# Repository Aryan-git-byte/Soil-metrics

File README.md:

<div align="center">

<h1>SoilMetrics</h1>

<h4><i>A Portable AI & IoT-Based Soil Health Monitoring Device</i></h4>

</div>

---

# Overview:

SoilMetrics is an **affordable soil health monitoring system** to measure key soil parameters in real time such as **NPK, EC, pH, Moisture, and Temperature.** which will allow small farmers to make scientific decision regarding their soil health and conditions which can help them do sustainable farming.

# What can it do?
This device can measure soil moisture, temperature, pH, electrical conductivity, and NPK. and then can send all that data to a cloud server using LTE. it also offers on device touch display to view sensor readings, ai reccomendations, weather reports etc. with help of offline sd card based data logging, and rechargeable 2S 18650 its a near perfect solution to deploy on farmsites for primary soil health monitoring.

## Hardware Specifications:

- **MCU** - [ESP32-S3-WROOM1U-N16R8](https://documentation.espressif.com/esp32-s3-wroom-1_wroom-1u_datasheet_en.pdf)
- **Cellular & GPS** - [SIM7080G](https://www.simcom.com/product/SIM7080G.html)
- **Soil Sensor** - [ZTS-3002-TR-\*-N01](https://robu-prod-media.s3.ap-south-1.amazonaws.com/uploads/2025/04/R224073R224074-ZTS-3002-TR-N01.pdf)
- **Display** - [SmartElex 3.5" TFT Resistive Touch Display 320x480](https://robu.in/product/smartelex-3-5-tft-resistive-touch-display-320x480/)

## Repo Structure:

```
SoilMetrics/
│
├── assets/   images
├── cad/       CAD source files & exports
├── firmware/       ESP-IDF firmware
├── kicad/          kicad source file
├── production/     BOM & gerber
│
├── README.md
├── LICENSE
└── JOURNAL.md
```

---

# Hardware:

## Schematic:

> Contains all the power realted things of the device including Type-c for programming, barrel jack for charging, BMS circuitory, Buck Converter and LDOs

> Contains the MCU, Buttons, LTE module, Receiver, SD card, sim slot etc

## PCB:

The hardware is designed on a 4 layer PCB, The complete design files are available [here](kicad/)

---

# Enclosure
| File | Download Link | Description|
|------|---------------|------------|
|Top Body Enclosure|[here](cad/src/Top-Body.f3d)|This is the source file of the top body
|Bottom plate|[here](cad/src/Bottom-Plate.f3d)|This is the source file of the Bottom plate
|Top Body Enclosure|[here](cad/exports/Top-Body.3mf)|This is the printable file of the top body
|Top Body Enclosure|[here](cad/exports/Bottom-Plate.3mf)|This is the printable file of the top body

---

# Firmware
> **Note:** The complete firmware is not available as of now, there are lot of things that can only be written after making actual hardware, so i will update the repo with complete firmware after build. For now its just a test code.

Configure ESP-IDF

```
idf.py set-target esp32s3
```

Build

```
idf.py build
```

---

## Flashing Firmware

Connect the board using USB.

Flash

```
idf.py flash
```

Open Serial Monitor

```
idf.py monitor
```

If flashing fails, place the board into download mode according to your ESP32-S3 hardware design and retry the command.

---
# How to Assemble

1. order all the components and pcb
2. solder them
3. flash the firmware
4. test it
5. 3d print the enclousure
6. put them all together

## Enclosure:
> Enclosure is not complete yet due to the online unavailability of 3d model of the Display. After getting the display i'll update the repo with correct files

---

# Bill of Materials

The completed BOM of the components used on PCB is in [production/bom.csv](production/bom.csv).

And expect those you need to order these:
|Component | Link | Price | 
|----------|------|-------|
|SmartElex 3.5" TFT Resistive Touch Display 320x480| [here](https://robu.in/product/smartelex-3-5-tft-resistive-touch-display-320x480/)|917 rs
| ZTS-3002-TR-*-N01|[here]( https://robu.in/product/multi-parameter-sensor/)|4396 rs
|2 x 18650 batteries | [here](https://robu.in/product/sony-vtc6-18650-li-ion-3000-mah-battery/)|699 rs each
| PCB + Stencil | | Sub-8K rs

---

*Made with 🔬🧪 ~~(science)~~ by aryan-git-byte*

```
# AI USE: AI has assisted me in firmware/

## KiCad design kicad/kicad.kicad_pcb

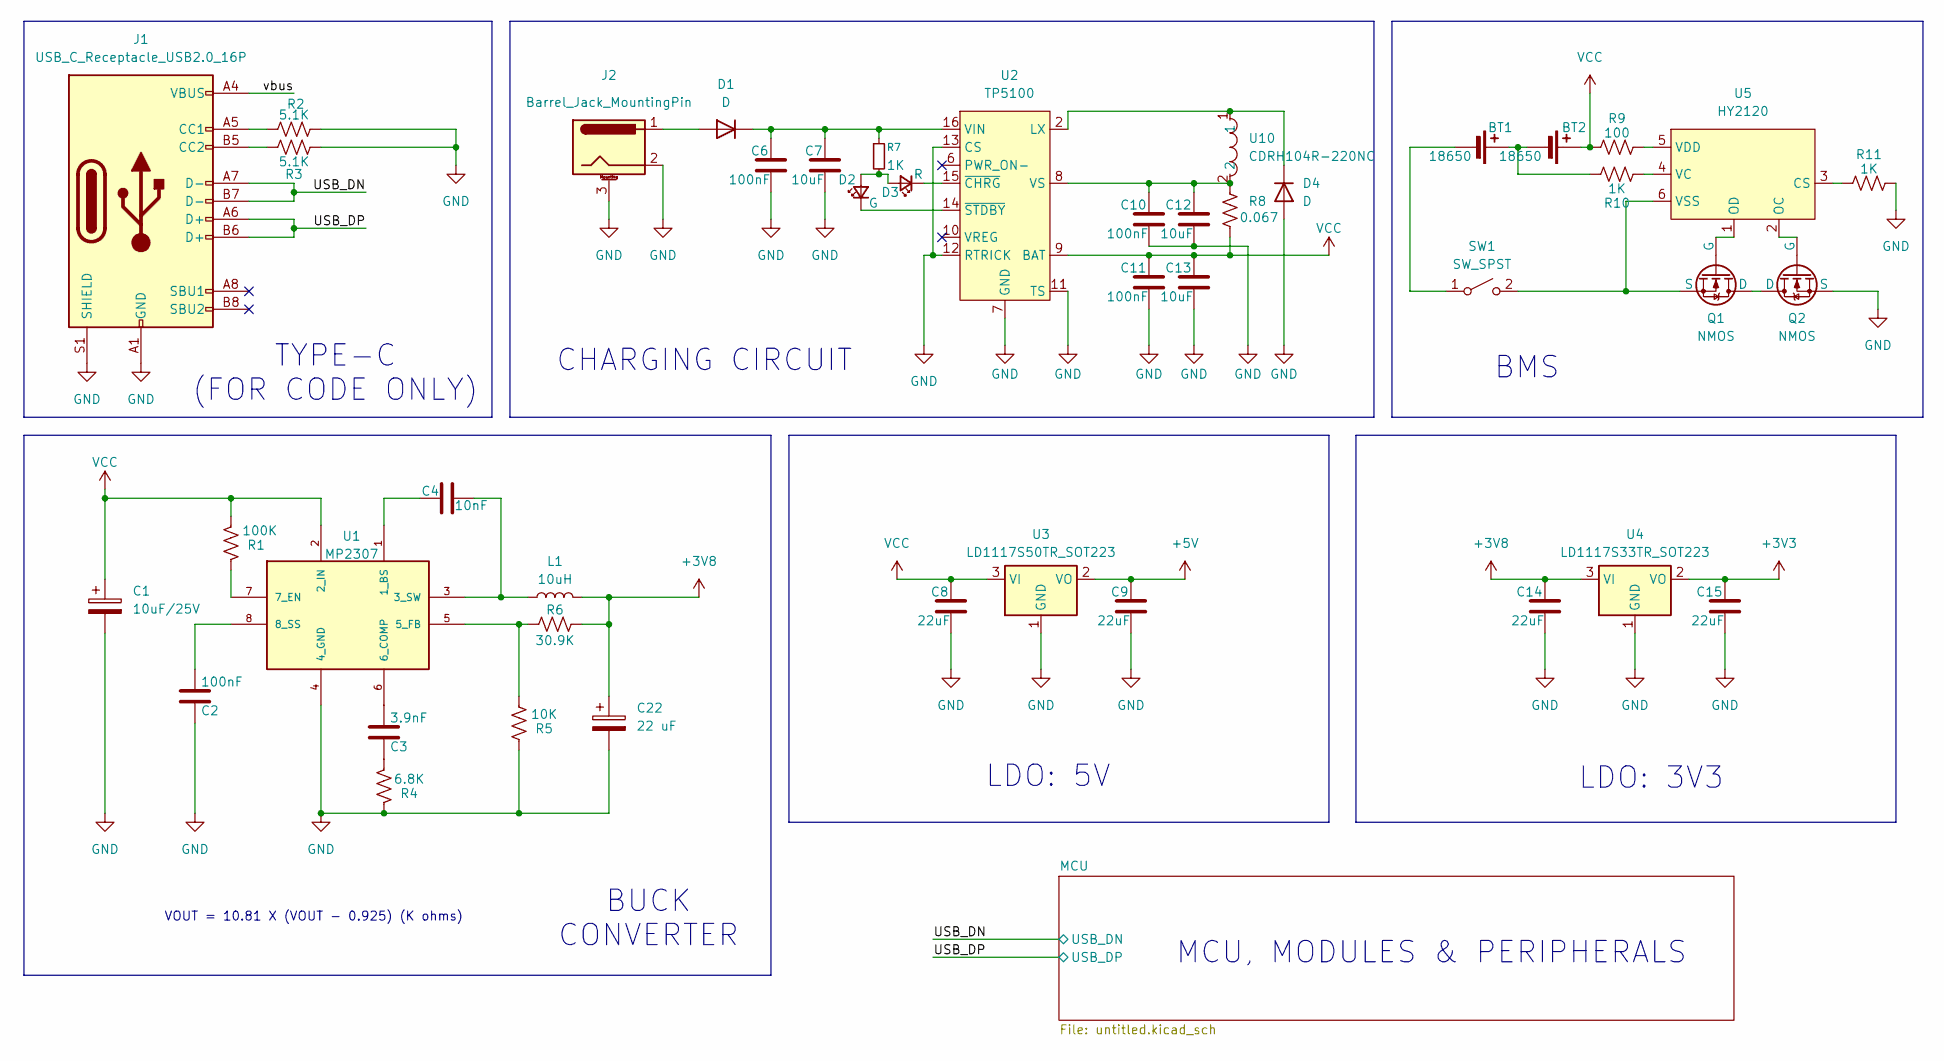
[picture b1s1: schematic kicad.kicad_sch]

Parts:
BT1, BT2: 18650; BatteryHolder_Keystone_1042_1x18650
C1: 10uF/25V; CP_Elec_6.3x5.4
C2, C6, C10, C11: 100nF; C_0805_2012Metric_Pad1.18x1.45mm_HandSolder
C3: 3.9nF; C_0805_2012Metric_Pad1.18x1.45mm_HandSolder
C4: 10nF; C_0805_2012Metric_Pad1.18x1.45mm_HandSolder
C7, C12, C13: 10uF; C_0805_2012Metric_Pad1.18x1.45mm_HandSolder
C8, C9, C14, C15: 22uF; C_0805_2012Metric_Pad1.18x1.45mm_HandSolder
C22: 22 uF; CP_Elec_5x5.3
D1, D4: D; D_SMA_Handsoldering
D2: G; LED_0805_2012Metric_Pad1.15x1.40mm_HandSolder
D3: R; LED_0805_2012Metric_Pad1.15x1.40mm_HandSolder
J1: USB_C_Receptacle_USB2.0_16P; USB_C_Receptacle_HRO_TYPE-C-31-M-12
J2: Barrel_Jack_MountingPin; BarrelJack_Horizontal
L1: 10uH; IND-SMD_L10.2-W10.0_SRR1050HA
Q1, Q2: NMOS; SOT-23
R1: 100K; R_0805_2012Metric_Pad1.20x1.40mm_HandSolder
R2, R3: 5.1K; R_0805_2012Metric_Pad1.20x1.40mm_HandSolder
R4: 6.8K; R_0805_2012Metric_Pad1.20x1.40mm_HandSolder
R5: 10K; R_0805_2012Metric_Pad1.20x1.40mm_HandSolder
R6: 30.9K; R_0805_2012Metric_Pad1.20x1.40mm_HandSolder
R7, R10, R11: 1K; R_0805_2012Metric_Pad1.20x1.40mm_HandSolder
R8: 0.067; R_1206_3216Metric_Pad1.30x1.75mm_HandSolder
R9: 100; R_0805_2012Metric_Pad1.20x1.40mm_HandSolder
SW1: SW_SPST; SW_Slide-03_Wuerth-WS-SLTV_10x2.5x6.4_P2.54mm
U1: MP2307; SOIC-8-1EP_3.9x4.9mm_P1.27mm_EP2.29x3mm_ThermalVias
U2: TP5100; QFN65P400X400X90-17N
U3: LD1117S50TR_SOT223; SOT-223-3_TabPin2
U4: LD1117S33TR_SOT223; SOT-223-3_TabPin2
U5: HY2120; SOT-23-6_Handsoldering
U10: CDRH104R-220NC; IND-SMD_L10.2-W10.0_SRR1050HA

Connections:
+3V3: C15.1, U4.2 (VO); also elsewhere on the board
+3V8: C14.1, C22.1, L1.2, R6.1, U4.3 (VI); also elsewhere on the board
+5V: C9.1, U3.2 (VO); also elsewhere on the board
/USB_DN: J1.A7 (D-), J1.B7 (D-); also elsewhere on the board
/USB_DP: J1.A6 (D+), J1.B6 (D+); also elsewhere on the board
/vbus: J1.A4 (VBUS), J1.A9 (VBUS), J1.B4 (VBUS), J1.B9 (VBUS)
GND: C1.2, C2.1, C6.2, C7.2, C8.2, C9.2, C10.2, C11.2, C12.2, C13.2, C14.2, C15.2, C22.2, D4.2 (A), J1.A1 (GND), J1.A12 (GND), J1.B1 (GND), J1.B12 (GND), J1.S1 (SHIELD), J2.2, J2.3 (MountPin_3), Q2.3 (S), R2.2, R3.1, R4.1, R5.2, R11.2, U1.4 (4_GND), U1.9 (4_GND), U2.7 (GND), U2.11 (TS), U2.12 (RTRICK), U2.13 (CS), U2.17 (EPAD), U3.1 (GND), U4.1 (GND); also elsewhere on the board
unnamed: BT1.1 (+), BT2.2 (-), R10.2
unnamed: BT1.2 (-), SW1.1 (A)
unnamed: C3.1, R4.2
unnamed: D1.2 (A), J2.1
unnamed: C6.1, C7.1, D1.1 (K), R7.1, U2.1 (VIN), U2.4 (VIN), U2.5 (VIN), U2.16 (VIN)
unnamed: D2.2 (A), D3.2 (A), R7.2
unnamed: D2.1 (K), U2.14 (~STDBY)
unnamed: D3.1 (K), U2.15 (~CHRG)
unnamed: D4.1 (K), U2.2 (LX), U2.3 (LX), U10.1
unnamed: J1.A5 (CC1), R2.1
unnamed: J1.B5 (CC2), R3.2
unnamed: Q1.1 (D), Q2.1 (D)
unnamed: Q1.2 (G), U5.1 (OD)
unnamed: Q1.3 (S), SW1.2 (B), U5.6 (VSS)
unnamed: Q2.2 (G), U5.2 (OC)
unnamed: C4.1, U1.1 (1_BS)
unnamed: C4.2, L1.1, U1.3 (3_SW)
unnamed: R5.1, R6.2, U1.5 (5_FB)
unnamed: C3.2, U1.6 (6_COMP)
unnamed: R1.1, U1.7 (7_EN)
unnamed: C2.2, U1.8 (8_SS)
unnamed: C10.1, C12.1, R8.1, U2.8 (VS), U10.2
unnamed: R11.1, U5.3 (CS)
unnamed: R10.1, U5.4 (VC)
unnamed: R9.2, U5.5 (VDD)
VCC: BT2.1 (+), C1.1, C8.1, C11.1, C13.1, R1.2, R8.2, R9.1, U1.2 (2_IN), U2.9 (BAT), U3.3 (VI)

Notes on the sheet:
LDO: 5V
BUCK CONVERTER
CHARGING CIRCUIT
VOUT = 10.81 X (VOUT - 0.925) (K ohms)
MCU, MODULES & PERIPHERALS
TYPE-C (FOR CODE ONLY)
LDO: 3V3
BMS

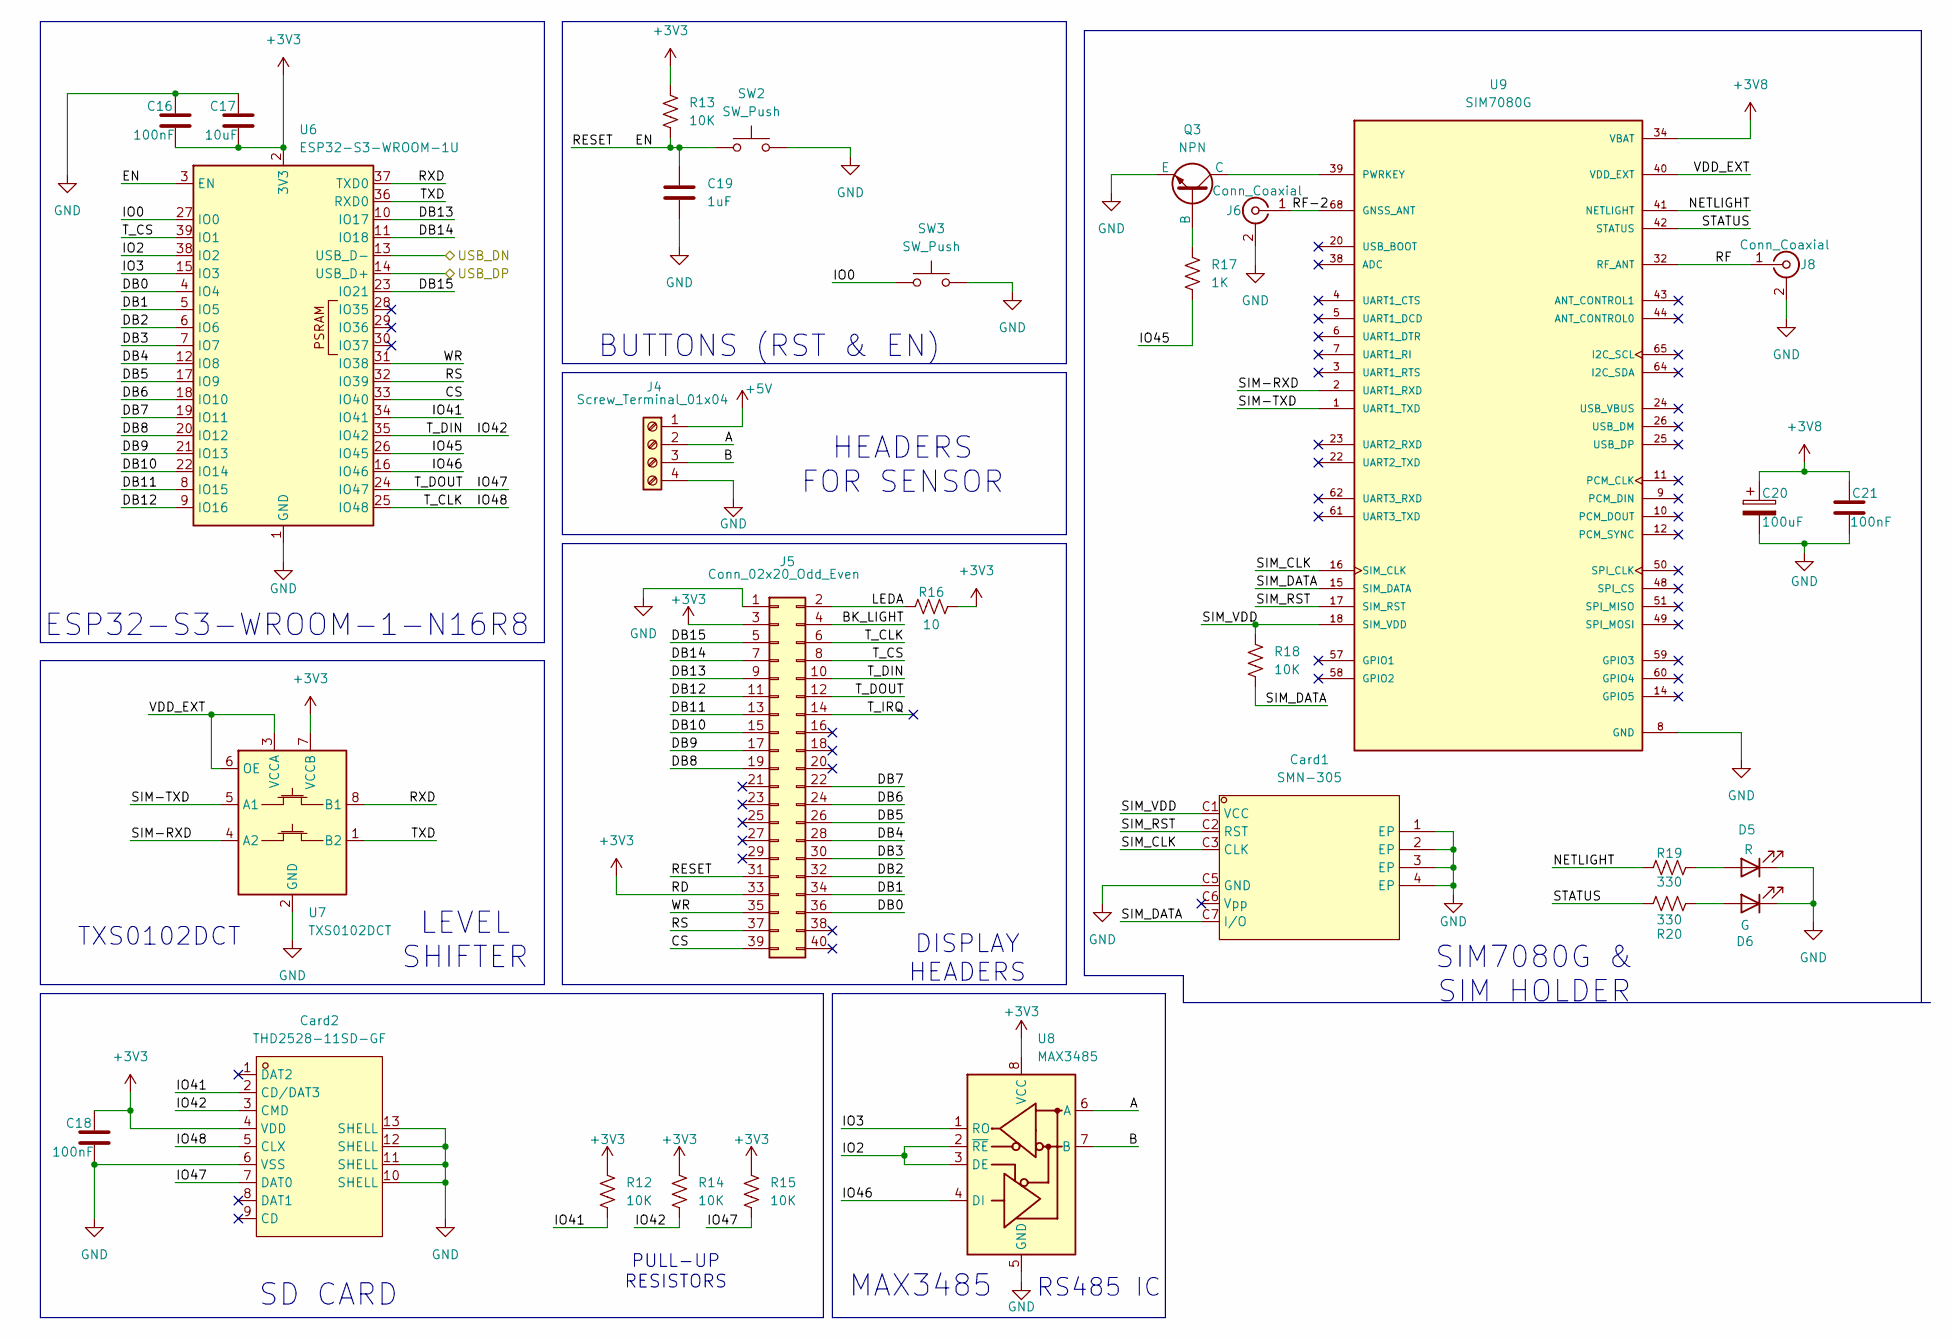
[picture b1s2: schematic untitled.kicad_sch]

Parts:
C16, C18, C21: 100nF; C_0805_2012Metric_Pad1.18x1.45mm_HandSolder
C17: 10uF; C_0805_2012Metric_Pad1.18x1.45mm_HandSolder
C19: 1uF; C_0805_2012Metric_Pad1.18x1.45mm_HandSolder
C20: 100uF; CP_EIA-3528-21_Kemet-B_HandSolder
Card1: SMN-305; SIM-SMD_SMN-305; MPN SMN-305; LCSC Part C266890
Card2: THD2528-11SD-GF; TF-SMD_THD2528-11SD-GF; MPN THD2528-11SD-GF; LCSC Part C283232
D5: R; LED_0805_2012Metric_Pad1.15x1.40mm_HandSolder
D6: G; LED_0805_2012Metric_Pad1.15x1.40mm_HandSolder
J4: Screw_Terminal_01x04; TerminalBlock_Phoenix_MKDS-1,5-4-5.08_1x04_P5.08mm_Horizont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
J5: Conn_02x20_Odd_Even; PinHeader_2x20_P2.54mm_Vertical
J6, J8: Conn_Coaxial; SMA_Amphenol_132289_EdgeMount
Q3: NPN; SOT-23
R12, R13, R14, R15, R18: 10K; R_0805_2012Metric_Pad1.20x1.40mm_HandSolder
R16: 10; R_0805_2012Metric_Pad1.20x1.40mm_HandSolder
R17: 1K; R_0805_2012Metric_Pad1.20x1.40mm_HandSolder
R19, R20: 330; R_0805_2012Metric_Pad1.20x1.40mm_HandSolder
SW2, SW3: SW_Push; SW_Tactile_SPST_NO_Straight_CK_PTS636Sx25SMTRLFS
U6: ESP32-S3-WROOM-1U
U7: TXS0102DCT; SSOP-8_2.95x2.8mm_P0.65mm
U8: MAX3485; SOIC-8_3.9x4.9mm_P1.27mm
U9: SIM7080G; XCVR_SIM7080G

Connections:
+3V3: C16.2, C17.2, C18.1, Card2.4 (VDD), J5.3, J5.33, R12.1, R13.1, R14.1, R15.1, R16.2, U6.2 (3V3), U7.7 (VCCB), U8.8 (VCC); also elsewhere on the board
+3V8: C20.1, C21.1, U9.34 (VBAT), U9.35 (VBAT); also elsewhere on the board
+5V: J4.1; also elsewhere on the board
/MCU/A: J4.2, U8.6 (A)
/MCU/B: J4.3, U8.7 (B)
/MCU/BK_LIGHT: J5.4
/MCU/CS: J5.39, U6.33 (IO40)
/MCU/DB0: J5.36, U6.4 (IO4)
/MCU/DB1: J5.34, U6.5 (IO5)
/MCU/DB2: J5.32, U6.6 (IO6)
/MCU/DB3: J5.30, U6.7 (IO7)
/MCU/DB4: J5.28, U6.12 (IO8)
/MCU/DB5: J5.26, U6.17 (IO9)
/MCU/DB6: J5.24, U6.18 (IO10)
/MCU/DB7: J5.22, U6.19 (IO11)
/MCU/DB8: J5.19, U6.20 (IO12)
/MCU/DB9: J5.17, U6.21 (IO13)
/MCU/DB10: J5.15, U6.22 (IO14)
/MCU/DB11: J5.13, U6.8 (IO15)
/MCU/DB12: J5.11, U6.9 (IO16)
/MCU/DB13: J5.9, U6.10 (IO17)
/MCU/DB14: J5.7, U6.11 (IO18)
/MCU/DB15: J5.5, U6.23 (IO21)
/MCU/EN: C19.1, J5.31, R13.2, SW2.1, U6.3 (EN)
/MCU/IO0: SW3.1, U6.27 (IO0)
/MCU/IO2: U6.38 (IO2), U8.2 (~RE), U8.3 (DE)
/MCU/IO3: U6.15 (IO3), U8.1 (RO)
/MCU/IO41: Card2.2 (CD/DAT3), R12.2, U6.34 (IO41)
/MCU/IO42: Card2.3 (CMD), J5.10, R14.2, U6.35 (IO42)
/MCU/IO45: R17.2, U6.26 (IO45)
/MCU/IO46: U6.16 (IO46), U8.4 (DI)
/MCU/IO47: Card2.7 (DAT0), J5.12, R15.2, U6.24 (IO47)
/MCU/IO48: Card2.5 (CLX), J5.6, U6.25 (IO48)
/MCU/LEDA: J5.2, R16.1
/MCU/NETLIGHT: R19.1, U9.41 (NETLIGHT)
/MCU/RF: J8.1 (In), U9.32 (RF_ANT)
/MCU/RF-2: J6.1 (In), U9.68 (GNSS_ANT)
/MCU/RS: J5.37, U6.32 (IO39)
/MCU/RXD: U6.37 (TXD0), U7.8 (B1)
/MCU/SIM-RXD: U7.4 (A2), U9.2 (UART1_RXD)
/MCU/SIM-TXD: U7.5 (A1), U9.1 (UART1_TXD)
/MCU/SIM_CLK: Card1.C3 (CLK), U9.16 (SIM_CLK)
/MCU/SIM_DATA: Card1.C7 (I/O), R18.2, U9.15 (SIM_DATA)
/MCU/SIM_RST: Card1.C2 (RST), U9.17 (SIM_RST)
/MCU/SIM_VDD: Card1.C1 (VCC), R18.1, U9.18 (SIM_VDD)
/MCU/STATUS: R20.1, U9.42 (STATUS)
/MCU/TXD: U6.36 (RXD0), U7.1 (B2)
/MCU/T_CS: J5.8, U6.39 (IO1)
/MCU/T_IRQ: J5.14
/MCU/VDD_EXT: U7.3 (VCCA), U7.6 (OE), U9.40 (VDD_EXT)
/MCU/WR: J5.35, U6.31 (IO38)
/USB_DN: U6.13 (USB_D-); also elsewhere on the board
/USB_DP: U6.14 (USB_D+); also elsewhere on the board
GND: C16.1, C17.1, C18.2, C19.2, C20.2, C21.2, Card1.1 (EP), Card1.2 (EP), Card1.3 (EP), Card1.4 (EP), Card1.C5 (GND), Card2.6 (VSS), Card2.10 (SHELL), Card2.11 (SHELL), Card2.12 (SHELL), Card2.13 (SHELL), D5.1 (K), D6.1 (K), J4.4, J5.1, J6.2 (Ext), J8.2 (Ext), Q3.3 (E), SW2.2, SW3.2, U6.1 (GND), U6.40 (GND), U6.41 (GND), U7.2 (GND), U8.5 (GND), U9.8 (GND), U9.13 (GND), U9.19 (GND), U9.21 (GND), U9.27 (GND), U9.28 (NC), U9.29 (NC), U9.30 (GND), U9.31 (GND), U9.33 (GND), U9.36 (GND), U9.37 (GND), U9.45 (GND), U9.46 (NC), U9.47 (NC), U9.52 (NC), U9.53 (NC), U9.54 (NC), U9.55 (NC), U9.56 (NC), U9.63 (GND), U9.66 (GND), U9.67 (GND), U9.69 (GND), U9.70 (GND), U9.71 (GND), U9.72 (GND), U9.73 (GND), U9.74 (GND), U9.75 (GND), U9.76 (GND), U9.77 (GND); also elsewhere on the board
unnamed: D5.2 (A), R19.2
unnamed: D6.2 (A), R20.2
unnamed: Q3.2 (B), R17.1
unnamed: Q3.1 (C), U9.39 (PWRKEY)

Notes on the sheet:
BUTTONS (RST & EN)
DISPLAY HEADERS
PULL-UP RESISTORS
LEVEL SHIFTER
ESP32-S3-WROOM-1-N16R8
SD CARD
HEADERS FOR SENSOR
SIM7080G & SIM HOLDER
MAX3485
TXS0102DCT
RS485 IC

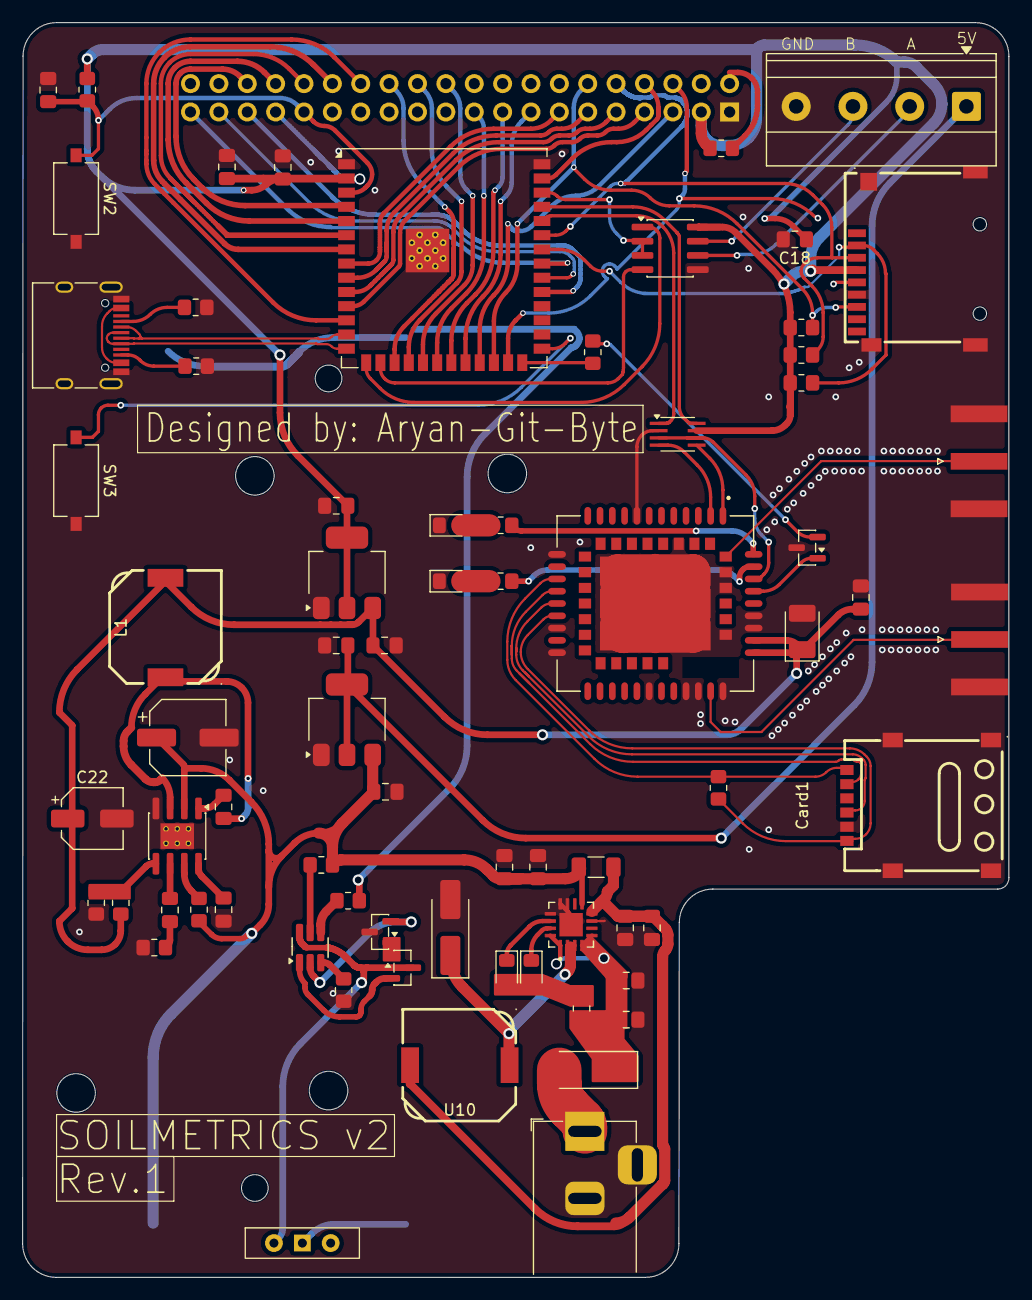
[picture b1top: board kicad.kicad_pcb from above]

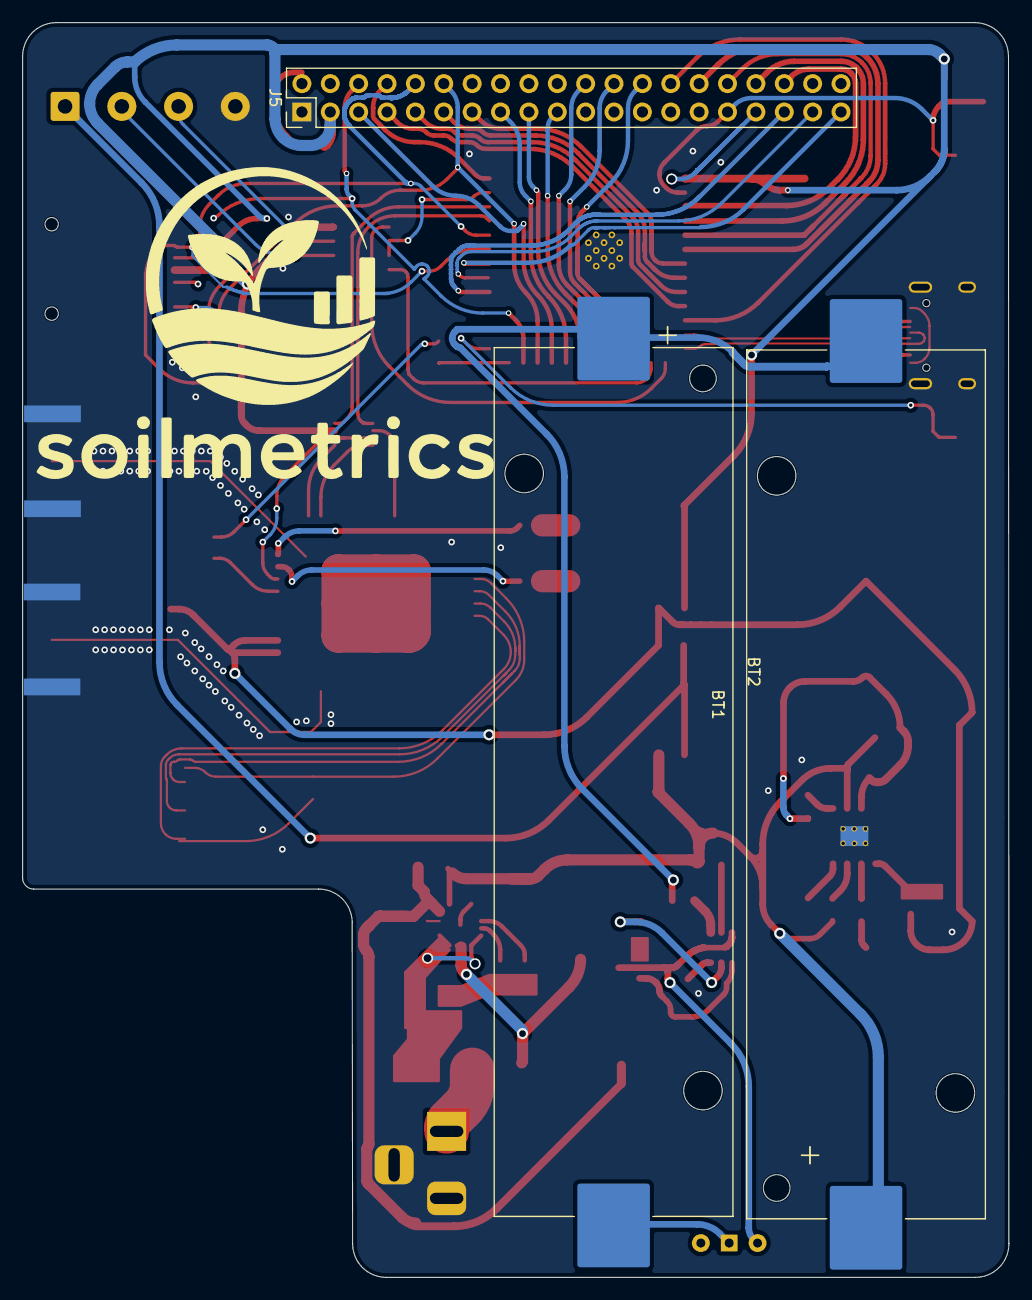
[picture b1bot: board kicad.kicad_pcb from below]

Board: 4 copper layers, 88.3 x 112.3 mm, 74 parts (3 on the bottom side), 83 nets.

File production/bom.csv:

"Reference","Qty","Value","Footprint","Price","Link"
"BT1,BT2","2","18650","Battery:BatteryHolder_Keystone_1042_1x18650","57.82","https://hubtronics.in/1s-18650-holder-smd?srsltid=AfmBOor3Tc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"
"C1","1","10uF/25V","Capacitor_SMD:CP_Elec_6.3x5.4","2.09","https://robu.in/product/efvl063ada100m0654-follon-10uf-63v-%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"
"C2,C6,C10,C11,C16,C18,C21","7","100nF","Capacitor_SMD:C_0805_2012Metric_Pad1.18x1.45mm_HandSolder","0.97","http://robu.in/product/tcc0805x7r104k500dt-cctc-smt-ceramic-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"
"C3","1","3.9nF","Capacitor_SMD:C_0805_2012Metric_Pad1.18x1.45mm_HandSolder","0.29","https://robu.in/product/tcc0805x7r392k500dt-cctc-smt-ceramic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"
"C4","1","10nF","Capacitor_SMD:C_0805_2012Metric_Pad1.18x1.45mm_HandSolder","1.39","https://robu.in/product/1-month-warranty-262/"
"C7,C12,C13,C17","4","10uF","Capacitor_SMD:C_0805_2012Metric_Pad1.18x1.45mm_HandSolder","3.24","https://robu.in/product/10uf-10000nf-25-v-capacitor-0805-smd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"
"C8,C9,C14,C15","4","22uF","Capacitor_SMD:C_0805_2012Metric_Pad1.18x1.45mm_HandSolder","9","https://robu.in/product/21br61a226me51k-murata-cap-smd-mlcc-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"
"C19","1","1uF","Capacitor_SMD:C_0805_2012Metric_Pad1.18x1.45mm_HandSolder","2.09","https://robu.in/product/1uf-1000nf-50v-capacitor-0805-smd-pa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"
"C20","1","100uF","Capacitor_Tantalum_SMD:CP_EIA-3528-21_Kemet-B_HandSolder","39","https://evelta.com/100uf-6-3v-10-case-b-tantalum-capacitor-b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"
"C22","1","22 uF","Capacitor_SMD:CP_Elec_5x5.3","1.94","https://robu.in/product/ves220m1etr-0505-lelon-22uf-25v-%C2%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"
"Card1","1","SMN-305","easyeda2kicad:SIM-SMD_SMN-305","35","https://robu.in/product/1-month-warranty-374/"
"Card2","1","THD2528-11SD-GF","easyeda2kicad:TF-SMD_THD2528-11SD-GF","41","http://robu.in/product/thd2528-11sd-gf-thd-2mm-connector-and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"
"D1,D4","2","D","Diode_SMD:D_SMA_Handsoldering","2.70","https://evelta.com/schottky-diode-1a-sma-ss110/"
"D2,D6","2","G","LED_SMD:LED_0805_2012Metric_Pad1.15x1.40mm_HandSolder","2.62","https://robu.in/product/0805-surface-mount-led-green-50-pcs/"
"D3,D5","2","R","LED_SMD:LED_0805_2012Metric_Pad1.15x1.40mm_HandSolder","1.44","https://robu.in/product/0805-surface-mount-led-red-50-pcs/"
"J1","1","USB_C_Receptacle_USB2.0_16P","Connector_USB:USB_C_Receptacle_HRO_TYPE-C-31-M-12","38","http://robu.in/product/type-c-31-m-12-hroparts-5a-1-16p-fema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"
"J2","1","Barrel_Jack_MountingPin","Connector_BarrelJack:BarrelJack_Horizontal","2.23","https://robu.in/product/dc-jack-005/"
"J4","1","Screw_Terminal_01x04","TerminalBlock_Phoenix:TerminalBlock_Phoenix_MKDS-1,5-4-5.08_1x04_P5.08mm_Horizontal","19","https://robu.in/product/4-pin-5-08mm-pitch-pluggable-screw-t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"
"J5","1","Conn_02x20_Odd_Even","Connector_PinHeader_2.54mm:PinHeader_2x20_P2.54mm_Vertical","12","https://robu.in/product/2-54mm-pitch-40-pin-male-double-row-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"
"J6,J8","2","Conn_Coaxial","Connector_Coaxial:SMA_Amphenol_132289_EdgeMount","65","https://robu.in/product/sma-female-straight-edge-pcb-mount-c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"
"L1","1","10uH","easyeda2kicad:IND-SMD_L10.2-W10.0_SRR1050HA","15","https://robu.in/product/cdrh104r-10%CE%BCh-power-inductor-pa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"
"Q1,Q2","2","NMOS","Package_TO_SOT_SMD:SOT-23","1.78","https://robu.in/product/cmn2310m-cmos-smd-mos-sot-23-n-field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"
"Q3","1","NPN","Package_TO_SOT_SMD:SOT-23","2.10","https://robu.in/product/mmbt2222-npn-transistor-pack-of-15/"
"R1","1","100K","Resistor_SMD:R_0805_2012Metric_Pad1.20x1.40mm_HandSolder","0.54","https://robu.in/product/yageo-100k-ohm-1-2w-0805-surface-mou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"
"R2,R3","2","5.1K","Resistor_SMD:R_0805_2012Metric_Pad1.20x1.40mm_HandSolder","1.57","https://robu.in/product/af0805fr-075k1l-yageo-5-1k%CF%89-%C2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"
"R4","1","6.8K","Resistor_SMD:R_0805_2012Metric_Pad1.20x1.40mm_HandSolder","0.87","https://robu.in/product/ac0805jr-076k8l-yageo-res-thick-film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"
"R5,R12,R13,R14,R15,R18","6","10K","Resistor_SMD:R_0805_2012Metric_Pad1.20x1.40mm_HandSolder","0.80","https://robu.in/product/rc0805fr-0710kl-yageo-res-thick-film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"
"R6","1","30.9K","Resistor_SMD:R_0805_2012Metric_Pad1.20x1.40mm_HandSolder","1.13","https://robu.in/product/ac0805fr-0730k9l-yageo-125mw-thick-f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"
"R7,R10,R11,R17","4","1K","Resistor_SMD:R_0805_2012Metric_Pad1.20x1.40mm_HandSolder","0.54","https://robu.in/product/1k-ohm-1-4w-0805-surface-mount-chip-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"
"R8","1","0.067","Resistor_SMD:R_1206_3216Metric_Pad1.30x1.75mm_HandSolder","2.08","https://robu.in/product/rl1206fr-070r068l-yageo-250mw-thick-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"
"R9","1","100","Resistor_SMD:R_0805_2012Metric_Pad1.20x1.40mm_HandSolder","0.35","https://robu.in/product/rc0805fr-07100rl-yageo-res-thick-fil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"
"R16","1","10","Resistor_SMD:R_0805_2012Metric_Pad1.20x1.40mm_HandSolder","3.87","https://robu.in/product/crcw080510r0fkeahp-vishay-smd-chip-r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"
"R19,R20","2","330","Resistor_SMD:R_0805_2012Metric_Pad1.20x1.40mm_HandSolder","0.80","https://robu.in/product/rc0805fr-07330rl-yageo-res-thick-fil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"
"SW1","1","SW_SPST","Button_Switch_THT:SW_Slide-03_Wuerth-WS-SLTV_10x2.5x6.4_P2.54mm","2.50","https://robu.in/product/ss-12f21g5-slide-1p2t-angled-switchh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"
"SW2,SW3","2","SW_Push","Button_Switch_SMD:SW_Tactile_SPST_NO_Straight_CK_PTS636Sx25SMTRLFS","3.81","https://robu.in/product/362-5mm-tactile-push-button-switch-20pcs/"
"U1","1","MP2307","Package_SO:SOIC-8-1EP_3.9x4.9mm_P1.27mm_EP2.29x3mm_ThermalVias","40","https://ifuturetech.org/product/mp2307-3a-23v-340khz-synchro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"
"U2","1","TP5100","Library:QFN65P400X400X90-17N","67","http://robu.in/product/tp5100-toppower-5v12v-lithium-ion-pol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"
"U3","1","LD1117S50TR_SOT223","Package_TO_SOT_SMD:SOT-223-3_TabPin2","17","https://robu.in/product/ld1117s50tr-stmicroelectronics-volta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"
"U4","1","LD1117S33TR_SOT223","Package_TO_SOT_SMD:SOT-223-3_TabPin2","17","https://robu.in/product/ld1117s50tr-stmicroelectronics-volta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"
"U5","1","HY2120","Package_TO_SOT_SMD:SOT-23-6_Handsoldering","21","https://robu.in/product/hy2120-cb-hycon-tech-1-5v10v-lithium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"
"U6","1","ESP32-S3-WROOM-1U","RF_Module:ESP32-S3-WROOM-1U","325","https://evelta.com/esp32-s3-wroom-1u-n16r8-wi-fi-ble-module-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"
"U7","1","TXS0102DCT","Package_SO:SSOP-8_2.95x2.8mm_P0.65mm","52","https://robu.in/product/txs0102dctt-texas-instruments-2-3v5-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"
"U8","1","MAX3485","Package_SO:SOIC-8_3.9x4.9mm_P1.27mm","218","https://robu.in/product/max3485esat-analog-devices-inc-maxim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"
"U9","1","SIM7080G","Library:XCVR_SIM7080G","2225","https://www.digikey.in/en/products/detail/simcom-wireless-so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"
"U10","1","CDRH104R-220NC","easyeda2kicad:IND-SMD_L10.2-W10.0_SRR1050HA","17","https://robu.in/product/cdrh104r-22%CE%BCh-power-inductor-pa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"

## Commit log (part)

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2026-04-11 git init
2026-05-28 migrating kicad from v9 to v10
2026-06-02 Completed the PCB
2026-06-06 Update STM32 TFT firmware for soil metrics display
2026-06-06 Improve soil metrics firmware integration
2026-06-19 Rename soilmetrics-journal.md to JOURNAL.md

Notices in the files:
README.md:
License: MIT
